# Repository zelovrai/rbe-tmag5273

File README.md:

# RBE TMAG5273 Qwiic Module

A compact, open-source breakout board for the **Texas Instruments TMAG5273** 3D Hall-effect sensor, featuring **Qwiic / STEMMA QT** connectivity. Designed by **Reka Bentuk Elektronika (RBE)**, this module makes it easy to integrate 3-axis magnetic field sensing, angle calculation, and proximity detection into your microcontroller projects without the hassle of soldering tiny SMD components.

<!-- TODO: Upload your 3D render to the repository and update the link below -->
<!--  -->
*(Replace the image link above with your actual 3D render stored in the repository)*

## 📖 Table of Contents
- [Features](#-features)
- [Hardware Overview](#-hardware-overview)
- [Pinout & Configuration](#-pinout--configuration)
- [Getting Started](#-getting-started)
- [Repository Structure](#-repository-structure)
- [Manufacturing & Assembly](#-manufacturing--assembly)
- [Contributing](#-contributing)
- [License](#-license)
- [Acknowledgments](#-acknowledgments)

## ✨ Features

*   **Sensor:** TI TMAG5273 (Low-power, linear 3D Hall-effect sensor).
*   **Interface:** I2C (Qwiic / STEMMA QT compatible).
*   **Connectivity:** 2x JST-SH 4-pin connectors (In/Out) for easy daisy-chaining.
*   **Breakout Headers:** Standard 2.54mm pitch headers for breadboard or direct wiring access.
*   **Interrupt Pin:** Dedicated `INT` pin broken out for configuring hardware interrupts.
*   **Operating Voltage:** 3.3V logic and power (Do not use 5V logic without level shifting).
*   **Mounting:** 4x M2/M2.5 mounting holes for secure installation.

## 🔌 Hardware Overview

The RBE TMAG5273 is designed with flexibility in mind. It features two Qwiic connectors for daisy-chaining multiple sensors on the same I2C bus, as well as dual 4-pin 2.54mm headers for traditional breadboard prototyping. 

### Pinout & Configuration

The module features two breakout header rows for flexible wiring options.

#### Top Header (I2C & Power)
| Pin | Label | Description |
| :--- | :--- | :--- |
| 1 | **GND** | Ground |
| 2 | **3V3** | Power Supply (3.3V) |
| 3 | **SDA** | I2C Data |
| 4 | **SCL** | I2C Clock |

#### Bottom Header (Power & Interrupt)
| Pin | Label | Description |
| :--- | :--- | :--- |
| 1 | **GND** | Ground |
| 2 | **GND** | Ground |
| 3 | **3V3** | Power Supply (3.3V) |
| 4 | **INT** | Interrupt Output (Active Low) |

#### Qwiic Connectors
*   **Left & Right:** JST-SH 4-pin (GND, 3.3V, SDA, SCL). Allows daisy-chaining with other Qwiic modules.

## 🚀 Getting Started

### Hardware Setup
1.  Connect the RBE TMAG5273 to your microcontroller using a standard Qwiic/STEMMA QT cable.
2.  Ensure your microcontroller operates at **3.3V logic**. If using a 5V board (like an Arduino Uno), use a logic level shifter on the SDA and SCL lines.
3.  The default I2C address for the TMAG5273 is typically `0x35`, but this can be changed via software configuration.

### Software Examples

#### Arduino IDE
Ensure you have the appropriate TMAG5273 library installed (e.g., from TI or SparkFun).

```cpp
#include <Wire.h>
#include "TMAG5273.h" // Replace with your actual library header

TMAG5273 sensor;

void setup() {
  Serial.begin(115200);
  Wire.begin();
  
  // Initialize sensor
  if (!sensor.begin()) {
    Serial.println("TMAG5273 sensor not detected. Check wiring!");
    while (1);
  }
  Serial.println("TMAG5273 sensor initialized.");
}

void loop() {
  // Read 3-axis magnetic field data
  float x = sensor.getX();
  float y = sensor.getY();
  float z = sensor.getZ();
  
  Serial.print("X: "); Serial.print(x);
  Serial.print(" | Y: "); Serial.print(y);
  Serial.print(" | Z: "); Serial.println(z);
  
  delay(100);
}
```

#### Raspberry Pi (Python)
Using the Adafruit CircuitPython library for the TMAG5273:

```python
import time
import board
import adafruit_tmag5273

i2c = board.I2C()  # uses board.SCL and board.SDA
sensor = adafruit_tmag5273.TMAG5273(i2c)

while True:
    print("X: %0.2f, Y: %0.2f, Z: %0.2f" % (sensor.magnetic[0], sensor.magnetic[1], sensor.magnetic[2]))
    time.sleep(0.1)
```

## 📂 Repository Structure

*   `/bom` - Contains the Interactive HTML BOM (`ibom.html`) for easy assembly and part sourcing.
*   `/library` - Custom KiCad libraries used in this project.
    *   `/3dmodels` - 3D STEP/IGES files for the sensor and connectors.
    *   `/footprints` - KiCad footprint libraries.
    *   `/symbols` - KiCad schematic symbols.
*   `*.kicad_pcb`, `*.kicad_pro`, `*.kicad_sch` - The main KiCad project files (Schematic and PCB layout).
*   `fp-lib-table`, `sym-lib-table` - KiCad library tables to ensure project portability.
*   `.gitignore` - Standard Git ignore file.

## 🛠️ Manufacturing & Assembly

To manufacture this PCB yourself:
1.  Open the project in **KiCad** (v6 or v7 recommended).
2.  Review the schematic and PCB layout to ensure it meets your requirements.
3.  Generate Gerber and Drill files (or use the provided KiCad files directly with your manufacturer like JLCPCB, PCBWay, or OSHPark).
4.  Use the `ibom.html` file in the `/bom` folder to easily source components and assist with SMD assembly.

**Recommended PCB Specs:**
*   Layers: 2
*   Thickness: 1.6mm
*   Surface Finish: HASL (Lead-free) or ENIG
*   Copper Weight: 1oz

## 🤝 Contributing

Contributions are always welcome! If you find a bug in the PCB design, want to improve the documentation, or add example code, please open an Issue or submit a Pull Request.

1. Fork the Project
2. Create your Feature Branch (`git checkout -b feature/AmazingFeature`)
3. Commit your Changes (`git commit -m 'Add some AmazingFeature'`)
4. Push to the Branch (`git push origin feature/AmazingFeature`)
5. Open a Pull Request

## 📜 License

This project is licensed under the **MIT License**. See the [LICENSE](LICENSE) file for details. You are free to modify, manufacture, and distribute this hardware, provided you retain attribution.

## 🙏 Acknowledgments

*   [Texas Instruments](https://www.ti.com/) for the TMAG5273 sensor.
*   [KiCad](https://kicad.org/) for the open-source EDA tool.
*   [SparkFun](https://www.sparkfun.com/) and [Adafruit](https://www.adafruit.com/) for the Qwiic/STEMMA QT standard.

---
Made with ❤️ by [Zelo Vrai](https://github.com/zelovrai) at **Reka Bentuk Elektronika (RBE)**.

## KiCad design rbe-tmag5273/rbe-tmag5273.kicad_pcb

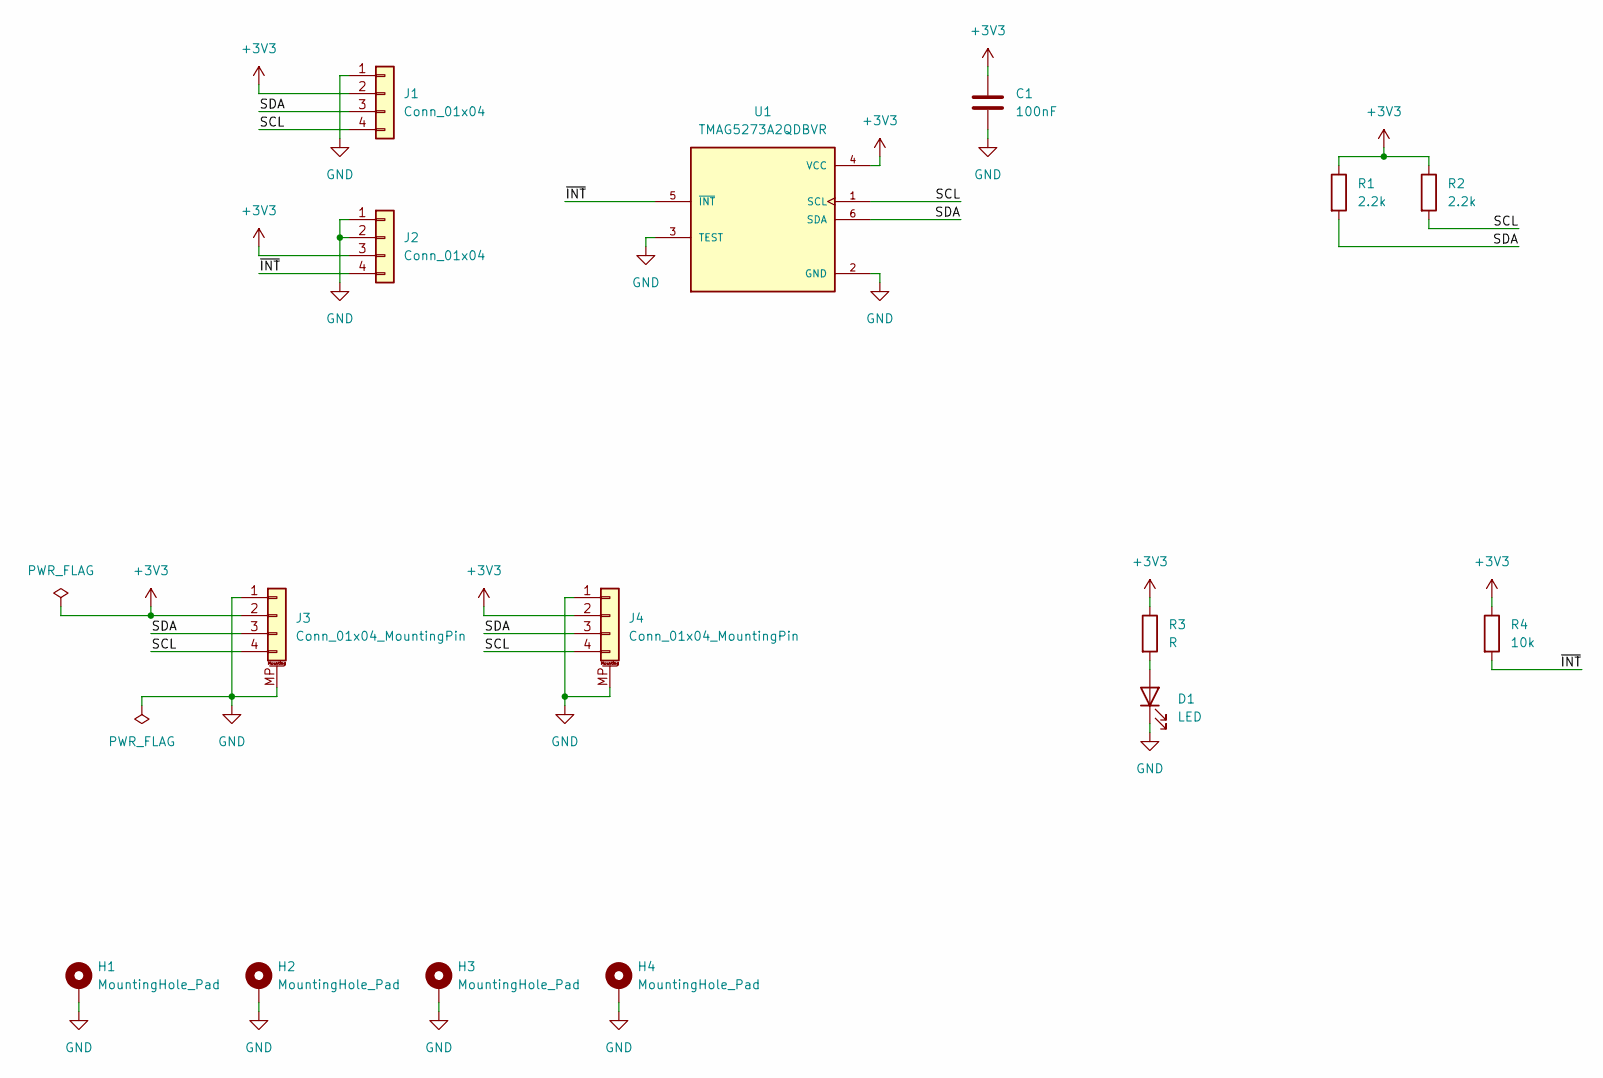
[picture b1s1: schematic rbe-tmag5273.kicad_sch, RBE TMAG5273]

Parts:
C1: 100nF; C_0603_1608Metric
D1: LED; LED_0603_1608Metric
H1, H2, H3, H4: MountingHole_Pad; MountingHole_3.2mm_M3_Pad
J1, J2: Conn_01x04; PinHeader_1x04_P2.54mm_Vertical
J3, J4: Conn_01x04_MountingPin; JST_SH_SM04B-SRSS-TB_1x04-1MP_P1.00mm_Horizontal
R1, R2: 2.2k; R_0603_1608Metric
R3: R; R_0603_1608Metric
R4: 10k; R_0603_1608Metric
U1: TMAG5273A2QDBVR; SOT95P280X140-6N; PARTREV B

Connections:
+3V3: C1.1, J1.2, J2.3, J3.2, J4.2, R1.1, R2.1, R3.1, R4.1, U1.4 (VCC)
/SCL: J1.4, J3.4, J4.4, R2.2, U1.1 (SCL)
/SDA: J1.3, J3.3, J4.3, R1.2, U1.6 (SDA)
/~INT: J2.4, R4.2, U1.5 (~INT)
GND: C1.2, D1.1 (K), H1.1 (1_1), H2.1 (1_1), H3.1 (1_1), H4.1 (1_1), J1.1, J2.1, J2.2, J3.1, J3.MP (MountPin), J4.1, J4.MP (MountPin), U1.2 (GND), U1.3 (TEST)
unnamed: D1.2 (A), R3.2

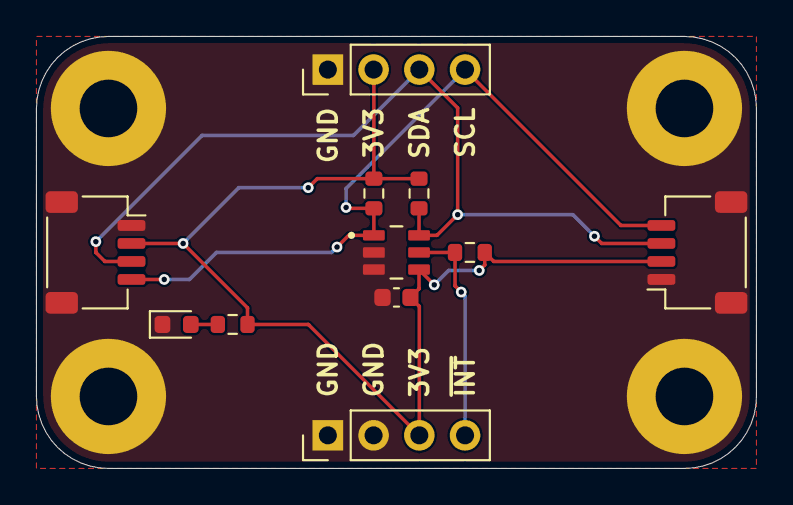
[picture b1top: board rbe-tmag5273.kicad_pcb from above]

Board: 2 copper layers, 40.0 x 24.0 mm, 15 parts (0 on the bottom side), 6 nets.

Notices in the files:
README.md:
License: MIT
